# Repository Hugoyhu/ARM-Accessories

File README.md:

# ARM-Accessories
Designs for ARM Prototyping Assistance

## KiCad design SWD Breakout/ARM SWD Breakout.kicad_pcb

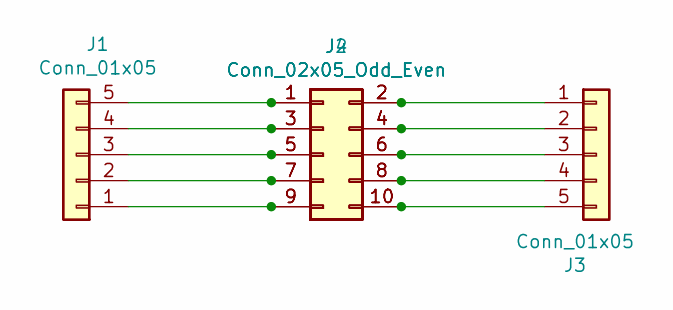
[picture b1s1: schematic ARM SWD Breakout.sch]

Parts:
J1, J3: Conn_01x05; PinSocket_1x05_P2.54mm_Vertical
J2: Conn_02x05_Odd_Even; PinSocket_2x05_P1.27mm_Vertical
J4: Conn_02x05_Odd_Even; PinSocket_2x05_P1.27mm_Vertical_SMD

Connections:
unnamed: J1.1, J2.9, J4.9
unnamed: J1.2, J2.7, J4.7
unnamed: J1.3, J2.5, J4.5
unnamed: J1.4, J2.3, J4.3
unnamed: J1.5, J2.1, J4.1
unnamed: J2.2, J3.1, J4.2
unnamed: J2.4, J3.2, J4.4
unnamed: J2.6, J3.3, J4.6
unnamed: J2.8, J3.4, J4.8
unnamed: J2.10, J3.5, J4.10

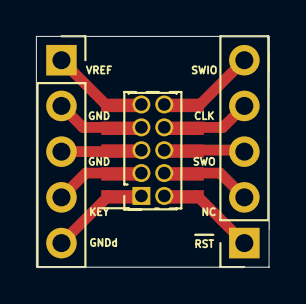
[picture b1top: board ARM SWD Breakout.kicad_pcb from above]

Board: 2 copper layers, 12.9 x 12.8 mm, 4 parts (0 on the bottom side), 10 nets.
